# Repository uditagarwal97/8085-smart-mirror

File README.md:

View this project on [CADLAB.io](https://cadlab.io/node/885). 

# 8085-smart-mirror
Open source project which aims at making a smart mirror using Intel 8085 with esp8266 as wifi interface.

# Project Abstract
Our smart mirror won’t just say you’re the prettiest of them all. It will also tell you the temperature, daily tasks(to-do list), weather outside, upcoming calendar appointments, and more. Encapsulated within a wooden frame, it will consist of a two-way mirror with an electronic display and wifi module behind the mirror. In form of widgets, it deploys various multi-colour LED's accompanied with stencils to form an iconic indicator for various weather conditions.

An essential part of modern interior designing ideas is the use of mirrors. Long gong are the days, when mirror is just used to see your face. Now, Mirrors being an integral part of every household are now used to provide glamorous user-interface for a variety of smart products. Our project, 8085 based smart mirror is an attempt to intermingle our modern luxury with a so called 'obsolete' Intel's microprocessor 8085. 

Main objective of our work is to keep the user updated with his To-Do list, which was once entered by the user, stored securely on a reliable cloud database. With our Smart Mirror android application interface, user can smoothly update the data, with his location (required for weather) along with the SSID and password of the wireless interface, being used for data exchange purpose.
Along with this, weather forecast along with temperature is displayed for user's convenience.

Please find the project related documenttaion files in the docs directory and the associated YouTube video can be found [here](https://www.youtube.com/watch?v=hadKsCXobCI).

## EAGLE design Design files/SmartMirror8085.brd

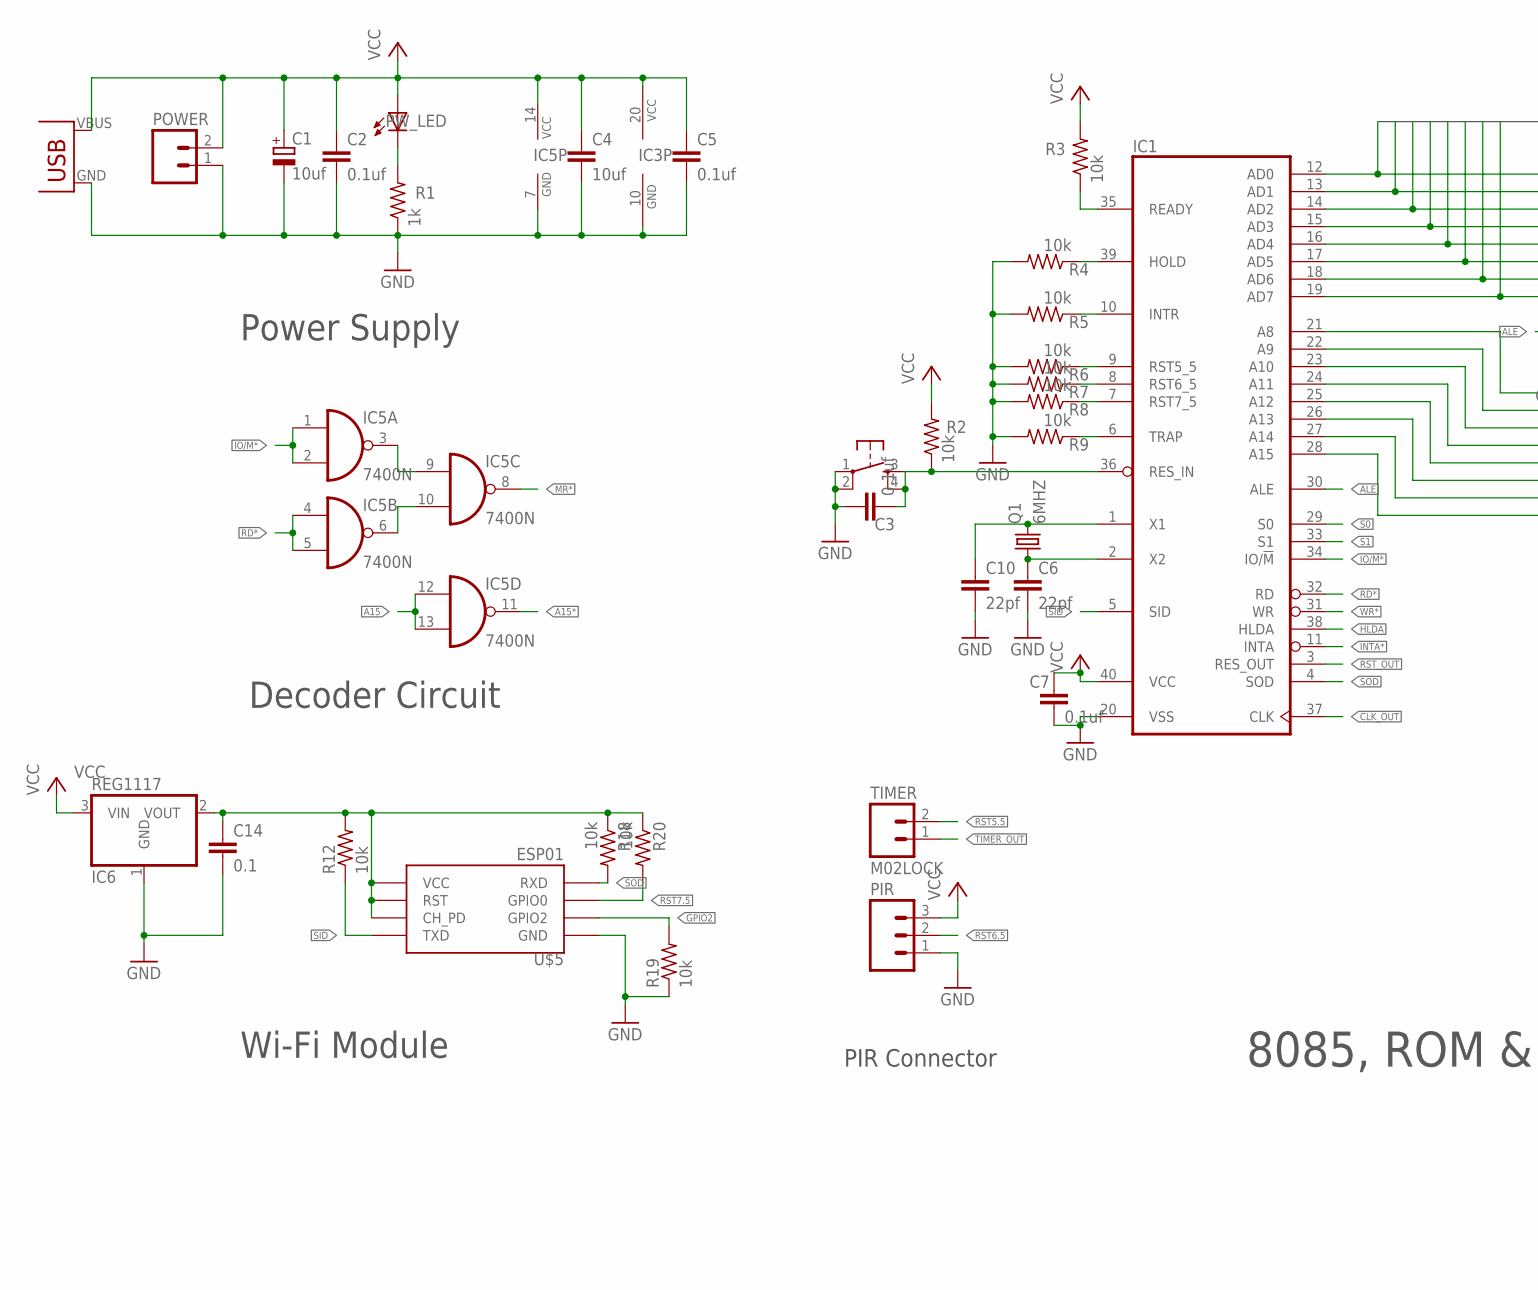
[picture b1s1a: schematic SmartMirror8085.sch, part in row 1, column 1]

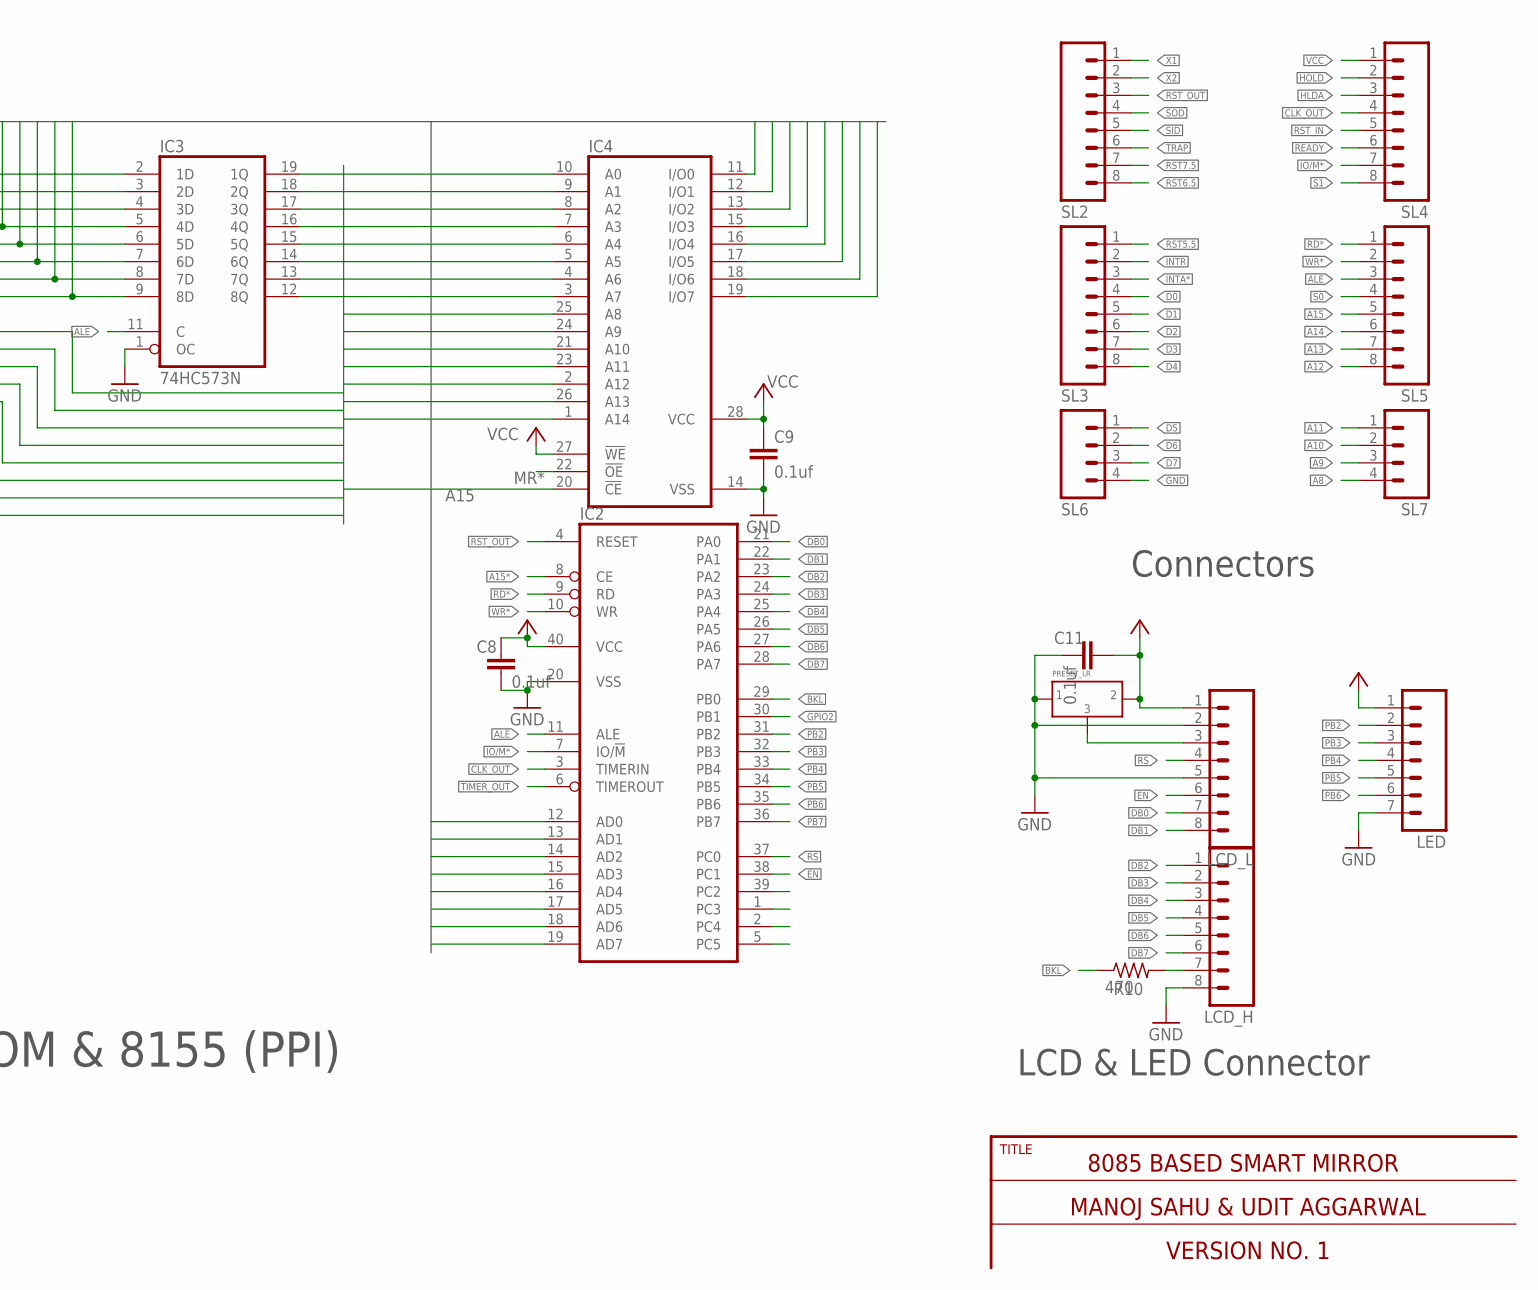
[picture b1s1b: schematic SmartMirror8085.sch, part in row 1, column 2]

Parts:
C1: 10uf; E5-8,5
C2, C3, C5, C7, C8, C9, C11: 0.1uf; C025-024X044
C4: 10uf; C025-024X044
C6, C10: 22pf; C025-024X044
C14: 0.1; C025-024X044
IC1: 8085; DIL40
IC2: 8155; DIL40
IC3: 74HC573N; DIL20
IC4: 58C256P; DIL28-6
IC5: 7400N; DIL14
IC6: REG1117; SOT223
LCD_H: M08; 08P
LCD_L: M08; 08P
LED: M07; 07P
PIR: M03; 03P
POWER: M02; 02P
PW_LED: LED3MM
Q1: 6MHZ; HC49US
R1: 1k; 0207/7
R2, R3, R4, R5, R6, R7, R8, R9, R12, R18, R19, R20: 10k; 0207/7
R10: 470; 0207/7
RESET: OMRON_SWITCH_10-XX; B3F-10XX
SL2, SL3, SL4, SL5: M08; 08P
SL6, SL7: M04; 04P
TIMER: M02LOCK; 1X02_LOCK
U$2: USB(POWER)
U$3: PRESET_LR
U$5: ESP01

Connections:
3V3: C14.1, IC6.2 (VOUT), R12.2, R18.1, R20.1, U$5.CH_PD, U$5.RST, U$5.VCC
A0: IC3.19 (1Q), IC4.10 (A0)
A1: IC3.18 (2Q), IC4.9 (A1)
A2: IC3.17 (3Q), IC4.8 (A2)
A3: IC3.16 (4Q), IC4.7 (A3)
A4: IC3.15 (5Q), IC4.6 (A4)
A5: IC3.14 (6Q), IC4.5 (A5)
A6: IC3.13 (7Q), IC4.4 (A6)
A7: IC3.12 (8Q), IC4.3 (A7)
A8: IC1.21 (A8), IC4.25 (A8), SL7.4
A9: IC1.22 (A9), IC4.24 (A9), SL7.3
A10: IC1.23 (A10), IC4.21 (A10), SL7.2
A11: IC1.24 (A11), IC4.23 (A11), SL7.1
A12: IC1.25 (A12), IC4.2 (A12), SL5.8
A13: IC1.26 (A13), IC4.26 (A13), SL5.7
A14: IC1.27 (A14), IC4.1 (A14), SL5.6
A15: IC1.28 (A15), IC4.20 (!CE), IC5.12 (I0), IC5.13 (I1), SL5.5
A15*: IC2.8 (CE), IC5.11 (O)
ALE: IC1.30 (ALE), IC2.11 (ALE), IC3.11 (C), SL5.3
BKL: IC2.29 (PB0), R10.1
CLK_OUT: IC1.37 (CLK), IC2.3 (TIMERIN), SL4.4
D0: IC1.12 (AD0), IC2.12 (AD0), IC3.2 (1D), IC4.11 (I/O0), SL3.4
D1: IC1.13 (AD1), IC2.13 (AD1), IC3.3 (2D), IC4.12 (I/O1), SL3.5
D2: IC1.14 (AD2), IC2.14 (AD2), IC3.4 (3D), IC4.13 (I/O2), SL3.6
D3: IC1.15 (AD3), IC2.15 (AD3), IC3.5 (4D), IC4.15 (I/O3), SL3.7
D4: IC1.16 (AD4), IC2.16 (AD4), IC3.6 (5D), IC4.16 (I/O4), SL3.8
D5: IC1.17 (AD5), IC2.17 (AD5), IC3.7 (6D), IC4.17 (I/O5), SL6.1
D6: IC1.18 (AD6), IC2.18 (AD6), IC3.8 (7D), IC4.18 (I/O6), SL6.2
D7: IC1.19 (AD7), IC2.19 (AD7), IC3.9 (8D), IC4.19 (I/O7), SL6.3
DB0: IC2.21 (PA0), LCD_L.7
DB1: IC2.22 (PA1), LCD_L.8
DB2: IC2.23 (PA2), LCD_H.1
DB3: IC2.24 (PA3), LCD_H.2
DB4: IC2.25 (PA4), LCD_H.3
DB5: IC2.26 (PA5), LCD_H.4
DB6: IC2.27 (PA6), LCD_H.5
DB7: IC2.28 (PA7), LCD_H.6
EN: IC2.38 (PC1), LCD_L.6
GND: C1.-, C2.2, C3.1, C4.2, C5.2, C6.2, C7.2, C8.2, C9.2, C10.2, C11.2, C14.2, IC1.20 (VSS), IC2.20 (VSS), IC3.1 (OC), IC3.10 (GND), IC4.14 (VSS), IC5.7 (GND), IC6.1 (GND), LCD_H.8, LCD_L.2, LCD_L.5, LED.7, PIR.1, POWER.1, R1.1, R4.2, R5.2, R6.2, R7.2, R8.2, R9.2, R19.1, RESET.1, RESET.2 (P1), SL6.4, U$2.GND, U$3.P$1 (1), U$5.GND
GPIO2: IC2.30 (PB1), R19.2, U$5.GPIO2
HLDA: IC1.38 (HLDA), SL4.3
HOLD: IC1.39 (HOLD), R4.1, SL4.2
INTA*: IC1.11 (INTA), SL3.3
INTR: IC1.10 (INTR), R5.1, SL3.2
IO/M*: IC1.34 (IO/!M), IC2.7 (IO/!M), IC5.1 (I0), IC5.2 (I1), SL4.7
MR*: IC4.22 (!OE), IC5.8 (O)
unnamed: LCD_L.3, U$3.P$3 (3)
unnamed: LCD_H.7, R10.2
unnamed: PW_LED.K (C), R1.2
unnamed: IC5.3 (O), IC5.9 (I0)
unnamed: IC5.6 (O), IC5.10 (I1)
PB2: IC2.31 (PB2), LED.2
PB3: IC2.32 (PB3), LED.3
PB4: IC2.33 (PB4), LED.4
PB5: IC2.34 (PB5), LED.5
PB6: IC2.35 (PB6), LED.6
PB7: IC2.36 (PB7)
RD*: IC1.32 (RD), IC2.9 (RD), IC5.4 (I0), IC5.5 (I1), SL5.1
READY: IC1.35 (READY), R3.1, SL4.6
RS: IC2.37 (PC0), LCD_L.4
RST5.5: IC1.9 (RST5_5), R6.1, SL3.1, TIMER.2
RST6.5: IC1.8 (RST6_5), PIR.2, R7.1, SL2.8
RST7.5: IC1.7 (RST7_5), R8.1, R20.2, SL2.7, U$5.GPIO0
RST_IN: C3.2, IC1.36 (RES_IN), R2.1, RESET.3 (S), RESET.4 (S1), SL4.5
RST_OUT: IC1.3 (RES_OUT), IC2.4 (RESET), SL2.3
S0: IC1.29 (S0), SL5.4
S1: IC1.33 (S1), SL4.8
SID: IC1.5 (SID), R12.1, SL2.5, U$5.TX (TXD)
SOD: IC1.4 (SOD), R18.2, SL2.4, U$5.RX (RXD)
TIMER_OUT: IC2.6 (TIMEROUT), TIMER.1
TRAP: IC1.6 (TRAP), R9.1, SL2.6
VCC: C1.+, C2.1, C4.1, C5.1, C7.1, C8.1, C9.1, C11.1, IC1.40 (VCC), IC2.40 (VCC), IC3.20 (VCC), IC4.27 (!WE), IC4.28 (VCC), IC5.14 (VCC), IC6.3 (VIN), LCD_L.1, LED.1, PIR.3, POWER.2, PW_LED.A, R2.2, R3.2, SL4.1, U$2.VBUS (VCC), U$3.P$2 (2)
WR*: IC1.31 (WR), IC2.10 (WR), SL5.2
X1: C10.1, IC1.1 (X1), Q1.2, SL2.1
X2: C6.1, IC1.2 (X2), Q1.1, SL2.2

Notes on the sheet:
TITLE
8085 BASED SMART MIRROR
MANOJ SAHU & UDIT AGGARWAL
VERSION NO. 1
Power Supply
Decoder Circuit
LCD & LED Connector
Connectors
8085, ROM & 8155 (PPI)
Wi-Fi Module
PIR Connector

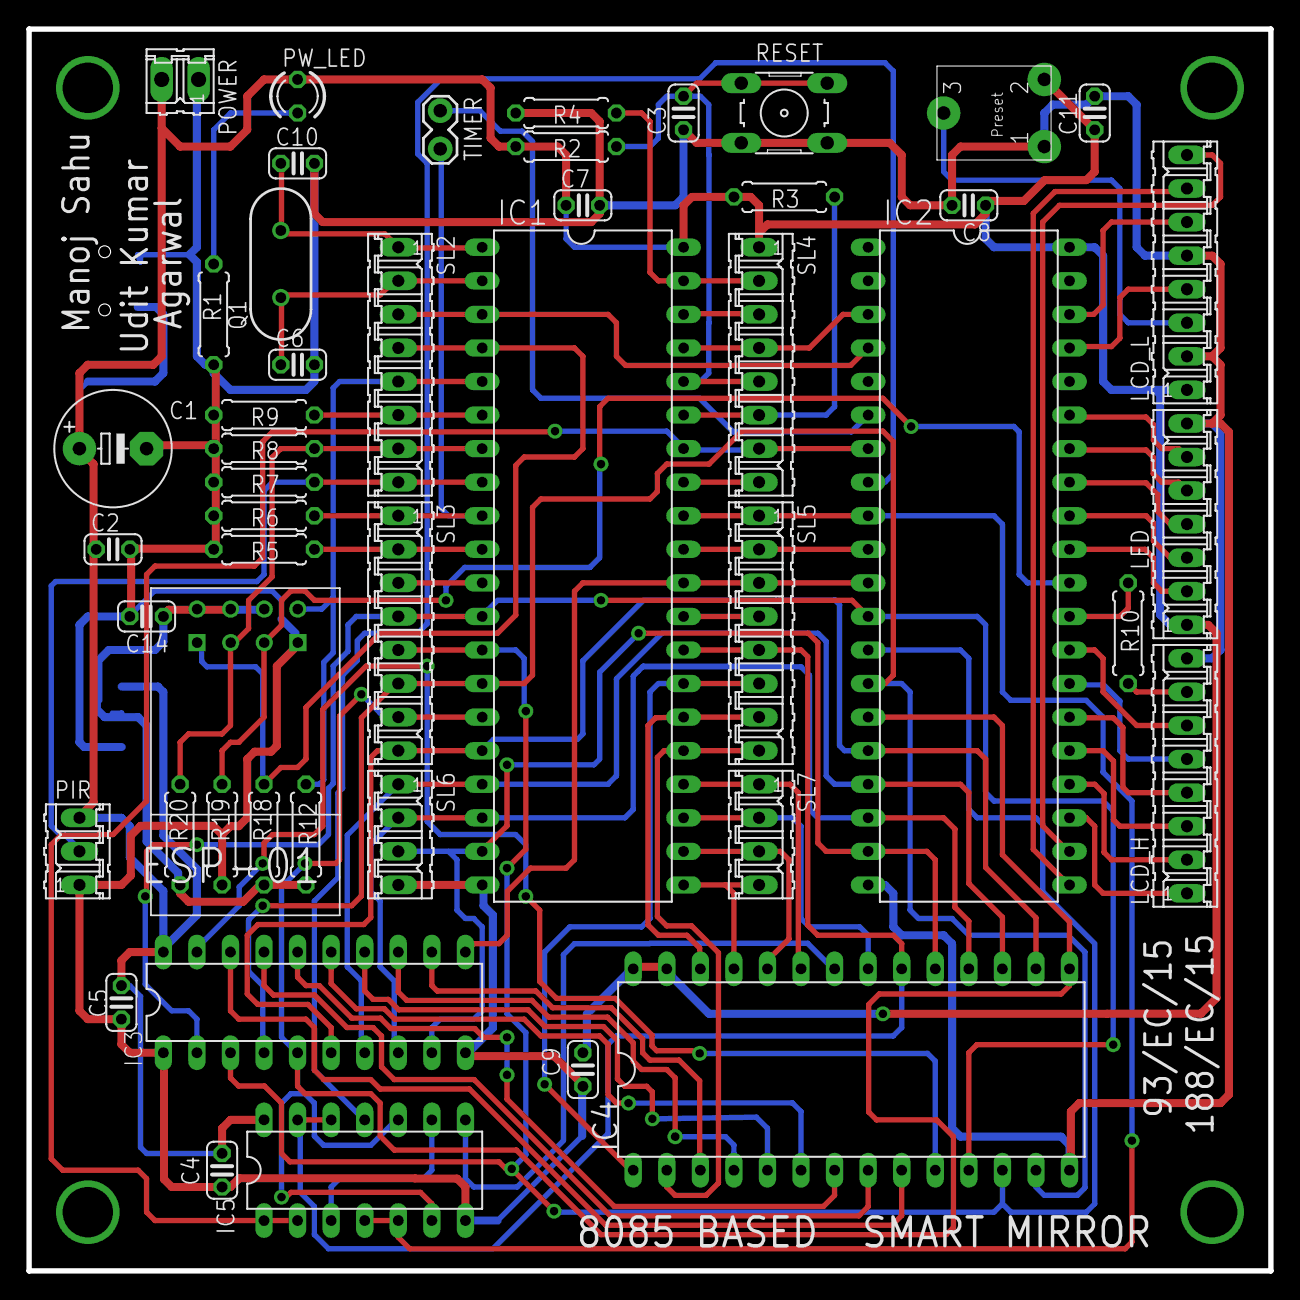
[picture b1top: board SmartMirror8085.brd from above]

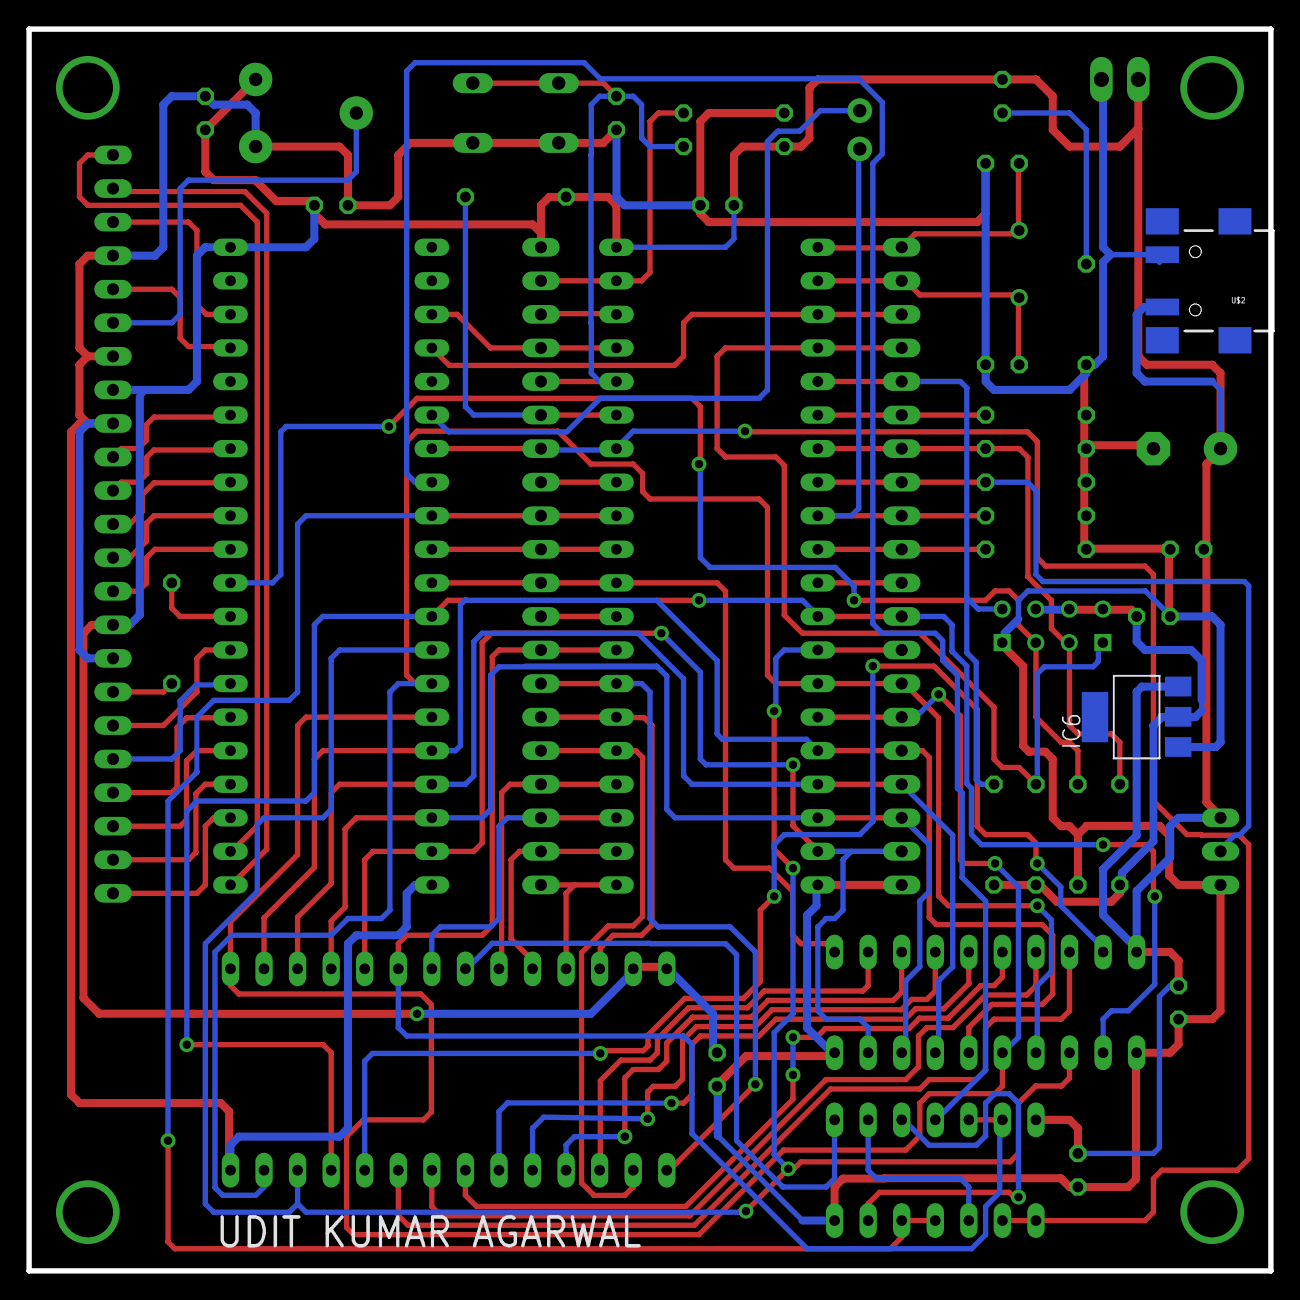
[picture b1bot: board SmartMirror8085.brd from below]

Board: 2 copper layers, 94.0 x 94.0 mm, 50 parts (2 on the bottom side), 74 nets.

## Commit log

2018-04-03 Added schematic
2018-04-15 Create LICENSE
2018-04-15 Update LICENSE
2018-04-15 Added design files and codes
2018-04-15 Backlink to CADLAB.io has been added.
2018-05-21 Added latest files
2018-05-22 Final working code[without weather]
2018-05-22 Final version including weather updates.
2019-10-01 Update README, Rearrange project files

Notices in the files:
parts and their libraries:
SparkFun-Connectors: Licensing: Creative Commons ShareAlike 4.0 International - https://creativecommons.org/licenses/by-sa/4.0
